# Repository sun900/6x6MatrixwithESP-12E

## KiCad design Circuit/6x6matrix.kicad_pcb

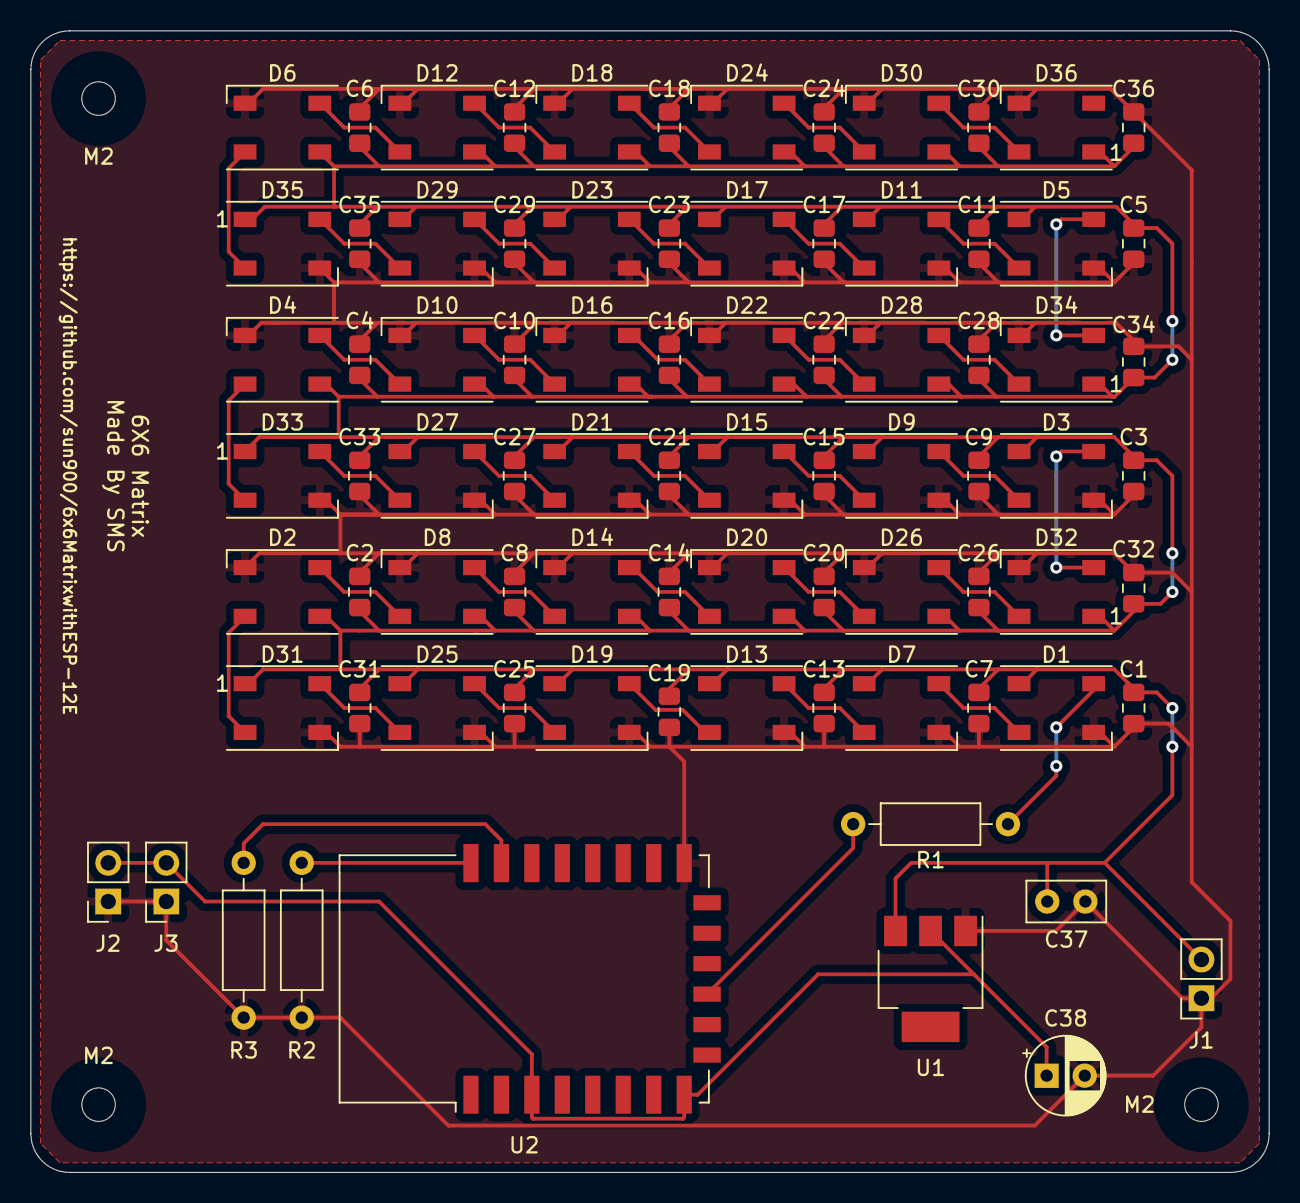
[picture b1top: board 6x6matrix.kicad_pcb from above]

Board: 2 copper layers, 81.3 x 74.9 mm, 85 parts (0 on the bottom side), 42 nets.

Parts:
C1, C2, C3, C4, C5, C6, C7, C8, C9, C10, C11, C12, C13, C14, C15, C16, C17, C18, C19, C20, C21, C22, C23, C24, C25, C26, C27, C28, C29, C30, C31, C32, C33, C34, C35, C36: 104; C_0805_2012Metric_Pad1.15x1.40mm_HandSolder
C37: 104; C_Disc_D5.0mm_W2.5mm_P2.50mm
C38: 10µF; CP_Radial_D5.0mm_P2.50mm
D1, D2, D3, D4, D5, D6, D7, D8, D9, D10, D11, D12, D13, D14, D15, D16, D17, D18, D19, D20, D21, D22, D23, D24, D25, D26, D27, D28, D29, D30, D31, D32, D33, D34, D35, D36: WS2812B; LED_WS2812B_PLCC4_5.0x5.0mm_P3.2mm
J1: Power; PinSocket_1x02_P2.54mm_Vertical
J2: SW1; PinSocket_1x02_P2.54mm_Vertical
J3: SW2; PinSocket_1x02_P2.54mm_Vertical
M2, M2#2, M2#3: MountingHole_2.2mm_M2
R1: 470; R_Axial_DIN0207_L6.3mm_D2.5mm_P10.16mm_Horizontal
R2, R3: 1k; R_Axial_DIN0207_L6.3mm_D2.5mm_P10.16mm_Horizontal
U1: AMS1117-3.3; SOT-223-3_TabPin2
U2: ESP-12E

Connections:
+3V3: C38.1, J2.2, J3.2, U1.2, U2.3, U2.8
+5V: C1.2, C2.2, C3.2, C4.2, C5.2, C6.2, C7.2, C8.2, C9.2, C10.2, C11.2, C12.2, C13.2, C14.2, C15.2, C16.2, C17.2, C18.2, C19.2, C20.2, C21.2, C22.2, C23.2, C24.2, C25.2, C26.2, C27.2, C28.2, C29.2, C30.2, C31.2, C32.2, C33.2, C34.2, C35.2, C36.2, C37.2, D1.1, D2.1, D3.1, D4.1, D5.1, D6.1, D7.1, D8.1, D9.1, D10.1, D11.1, D12.1, D13.1, D14.1, D15.1, D16.1, D17.1, D18.1, D19.1, D20.1, D21.1, D22.1, D23.1, D24.1, D25.1, D26.1, D27.1, D28.1, D29.1, D30.1, D31.1, D32.1, D33.1, D34.1, D35.1, D36.1, J1.2, U1.3
GND: C1.1, C2.1, C3.1, C4.1, C5.1, C6.1, C7.1, C8.1, C9.1, C10.1, C11.1, C12.1, C13.1, C14.1, C15.1, C16.1, C17.1, C18.1, C19.1, C20.1, C21.1, C22.1, C23.1, C24.1, C25.1, C26.1, C27.1, C28.1, C29.1, C30.1, C31.1, C32.1, C33.1, C34.1, C35.1, C36.1, C37.1, C38.2, D1.3, D2.3, D3.3, D4.3, D5.3, D6.3, D7.3, D8.3, D9.3, D10.3, D11.3, D12.3, D13.3, D14.3, D15.3, D16.3, D17.3, D18.3, D19.3, D20.3, D21.3, D22.3, D23.3, D24.3, D25.3, D26.3, D27.3, D28.3, D29.3, D30.3, D31.3, D32.3, D33.3, D34.3, D35.3, D36.3, J1.1, J2.1, J3.1, R2.2, R3.2, U1.1, U2.15
GPIO_LED: D1.4, R1.1
GPIO_SW_Conn_1: R2.1, U2.22
GPIO_SW_Conn_2: R3.1, U2.21
unnamed: D1.2, D7.4
unnamed: D2.2, D8.4
unnamed: D2.4, D31.2
unnamed: D3.2, D9.4
unnamed: D3.4, D32.2
unnamed: D10.2, D16.4
unnamed: D4.2, D10.4
unnamed: D11.2, D17.4
unnamed: D5.2, D11.4
unnamed: D12.2, D18.4
unnamed: D6.2, D12.4
unnamed: D13.2, D19.4
unnamed: D7.2, D13.4
unnamed: D14.2, D20.4
unnamed: D8.2, D14.4
unnamed: D15.2, D21.4
unnamed: D9.2, D15.4
unnamed: D16.2, D22.4
unnamed: D17.2, D23.4
unnamed: D18.2, D24.4
unnamed: D19.2, D25.4
unnamed: D20.2, D26.4
unnamed: D21.2, D27.4
unnamed: D22.2, D28.4
unnamed: D23.2, D29.4
unnamed: D24.2, D30.4
unnamed: D25.2, D31.4
unnamed: D26.2, D32.4
unnamed: D27.2, D33.4
unnamed: D28.2, D34.4
unnamed: D29.2, D35.4
unnamed: D30.2, D36.4
unnamed: D4.4, D33.2
unnamed: D5.4, D34.2
unnamed: D6.4, D35.2
unnamed: R1.2, U2.11

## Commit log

2020-10-15 FIX : ESP-12,Switch,LEDdata
    only fixed schematic of EPS-12E, Switch, LED data
2020-10-15 Made Folder
